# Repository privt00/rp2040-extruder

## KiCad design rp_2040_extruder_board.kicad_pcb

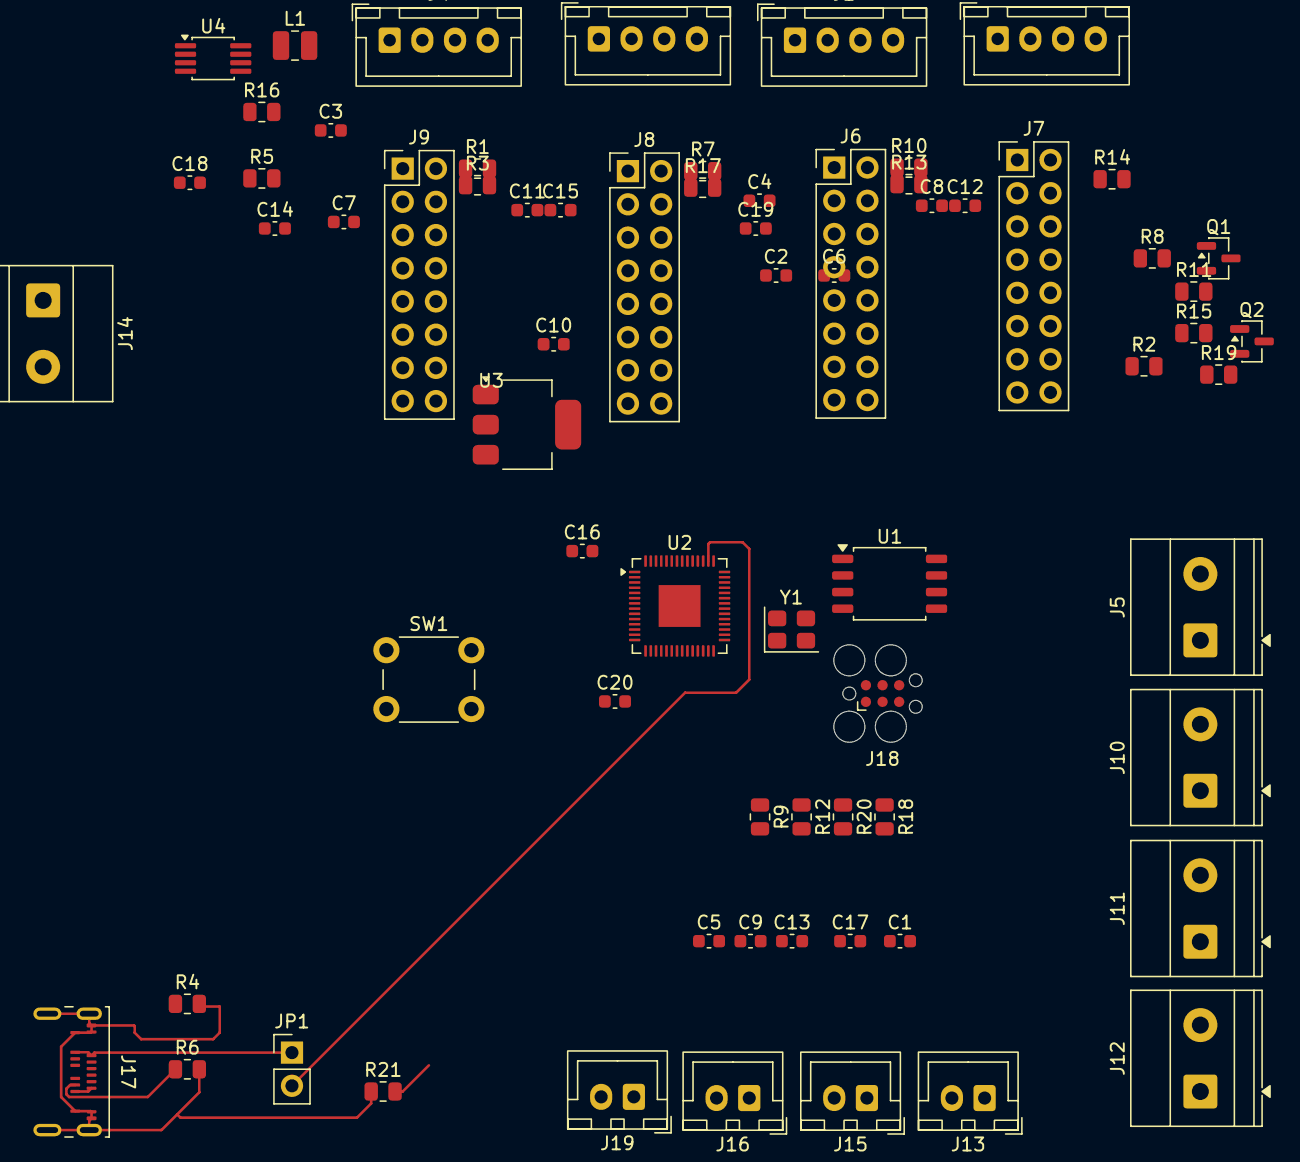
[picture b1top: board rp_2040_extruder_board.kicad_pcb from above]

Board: 2 copper layers, 70 parts (0 on the bottom side), 69 nets.

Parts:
C1, C2, C3, C5, C8, C9, C10, C11, C13, C17, C18, C19: 100nF; C_0603_1608Metric
C4, C7, C12, C15: 47µF; C_0603_1608Metric
C6: 1µF; C_0603_1608Metric
C14: 30µF; C_0603_1608Metric
C16, C20: 22 pF; C_0603_1608Metric
J1, J2, J3, J4: Conn_01x04; JST_XH_B4B-XH-A_1x04_P2.50mm_Vertical
J5, J10, J11, J12, J14: Screw_Terminal_01x02; TerminalBlock_Phoenix_MKDS-1,5-2-5.08_1x02_P5.08mm_Horizont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
J6, J7, J8, J9: Conn_02x08_Odd_Even; PinHeader_2x08_P2.54mm_Vertical
J13, J15, J16, J19: Conn_01x02; JST_XH_B2B-XH-A_1x02_P2.50mm_Vertical
J17: USB_C_Receptacle; USB_C_Receptacle_Amphenol_124019772112A
J18: Conn_ARM_SWD_TagConnect_TC2030; Tag-Connect_TC2030-IDC-FP_2x03_P1.27mm_Vertical
JP1: Jumper_2_Open; PinHeader_1x02_P2.54mm_Vertical
L1: L; L_1008_2520Metric
Q1, Q2: AO3400A; SOT-23
R1, R7, R10, R14: 10kΩ; R_0805_2012Metric
R2, R3, R13, R17: 4.7kΩ; R_0805_2012Metric
R4, R6: 5.1kΩ; R_0805_2012Metric
R5: 10 kΩ; R_0805_2012Metric
R8, R15: 100Ω; R_0805_2012Metric
R9, R12, R18, R20: 4.7k; R_0805_2012Metric
R11, R19: 100kΩ; R_0805_2012Metric
R16: 52.5 kΩ; R_0805_2012Metric
R21: R; R_0805_2012Metric
SW1: SW_Push; SW_PUSH_6mm
U1: W25Q16JVSS; SOIC-8_5.3x5.3mm_P1.27mm
U2: RP2040; QFN-56-1EP_7x7mm_P0.4mm_EP3.2x3.2mm
U3: AMS1117-3.3; SOT-223-3_TabPin2
U4: TPS62160DGK; MSOP-8_3x3mm_P0.65mm
Y1: Crystal; Crystal_SMD_3225-4Pin_3.2x2.5mm

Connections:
+3.3V: C1.2, C2.2, C5.2, C6.2, C9.2, C10.1, C13.2, C17.2, J6.3, J7.3, J8.3, J9.3, J18.1 (VCC), R1.2, R7.2, R10.2, R14.2, U1.8 (VCC), U2.1 (IOVDD), U2.10 (IOVDD), U2.22 (IOVDD), U2.23 (DVDD), U2.33 (IOVDD), U2.42 (IOVDD), U2.43 (ADC_AVDD), U2.48 (USB_VDD), U2.49 (IOVDD), U2.50 (DVDD), U3.2 (VO)
+5V: L1.2, R16.1, U3.3 (VI), U4.6 (VOS)
+12V: C3.2, C4.2, C7.2, C8.2, C11.2, C12.2, C14.1, C15.2, C18.1, C19.2, J5.1, J6.15, J7.15, J8.15, J9.15, J10.1, J11.1, J12.1, J14.1, U4.2 (VIN), U4.3 (EN)
/5V_MAIN: JP1.2 (B), U2.44 (VREG_VIN)
/RX PIN: R2.2, R3.2, R13.2, R17.2, U2.17 (GPIO14)
/VBUS_USB: J17.A4 (VBUS), J17.A9 (VBUS), J17.B4 (VBUS), J17.B9 (VBUS), JP1.1 (A)
GND: C1.1, C2.1, C3.1, C4.1, C5.1, C6.1, C7.1, C8.1, C9.1, C10.2, C11.1, C12.1, C13.1, C14.2, C15.1, C16.2, C17.1, C18.2, C19.1, C20.2, J5.2, J6.1, J6.12, J6.13, J6.14, J7.1, J7.12, J7.13, J7.14, J8.1, J8.12, J8.13, J8.14, J9.1, J9.12, J9.13, J9.14, J10.2, J11.2, J12.2, J13.1, J14.2, J15.1, J16.1, J17.A1 (GND), J17.A12 (GND), J17.B1 (GND), J17.B12 (GND), J17.SH (SHIELD), J18.5 (GND), J19.1, Q1.2 (S), Q1.3 (D), Q2.2 (S), Q2.3 (D), R4.2, R5.2, R6.2, R11.2, R19.2, R21.1, SW1.2, U1.4 (GND), U2.19 (TESTEN), U2.57 (GND), U3.1 (GND), U4.1 (PGND), U4.4 (AGND)
unnamed: J9.2, U2.3 (GPIO1)
unnamed: J9.4, U2.2 (GPIO0)
unnamed: J4.1, J9.5
unnamed: J4.4, J9.7
unnamed: J9.8, R1.1
unnamed: J4.3, J9.9
unnamed: J9.10, R3.1
unnamed: J4.2, J9.11
unnamed: J6.16, J7.16, J8.16, J9.16, U2.11 (GPIO8)
unnamed: J8.2, U2.5 (GPIO3)
unnamed: J8.4, U2.4 (GPIO2)
unnamed: J3.1, J8.5
unnamed: J3.4, J8.7
unnamed: J8.8, R7.1
unnamed: J3.3, J8.9
unnamed: J8.10, R17.1
unnamed: J3.2, J8.11
unnamed: J6.2, U2.7 (GPIO5)
unnamed: J6.4, U2.6 (GPIO4)
unnamed: J1.1, J6.5
unnamed: J1.4, J6.7
unnamed: J6.8, R10.1
unnamed: J1.3, J6.9
unnamed: J6.10, R13.1
unnamed: J1.2, J6.11
unnamed: J7.2, U2.9 (GPIO7)
unnamed: J7.4, R8.2, U2.8 (GPIO6), U2.12 (GPIO9)
unnamed: J7.8, R14.1
unnamed: J7.10, R2.1
unnamed: J17.A5 (CC1), R4.1
unnamed: J17.B5 (CC2), R6.1
unnamed: J17.A8 (SBU1), J17.B8 (SBU2)
unnamed: J2.1, J7.5
unnamed: J2.2, J7.11
unnamed: J2.3, J7.9
unnamed: J2.4, J7.7
unnamed: J18.4 (SWCLK), U2.24 (SWCLK)
unnamed: J18.2 (SWDIO), U2.25 (SWDIO)
unnamed: J18.3 (~RESET), R21.2, SW1.1, U2.26 (RUN)
unnamed: J13.2, R18.2
unnamed: J15.2, R20.2
unnamed: J16.2, R12.2
unnamed: J19.2, R9.2
unnamed: Q1.1 (G), R8.1, R11.1
unnamed: Q2.1 (G), R15.1, R19.1
unnamed: R15.2, U2.13 (GPIO10)
unnamed: R18.1, U2.38 (GPIO26/ADC0)
unnamed: R20.1, U2.39 (GPIO27/ADC1)
unnamed: R12.1, U2.40 (GPIO28/ADC2)
unnamed: R9.1, U2.41 (GPIO29/ADC3)
unnamed: U1.6 (CLK), U2.52 (QSPI_SCLK)
unnamed: U1.5 (DI/IO_{0}), U2.53 (QSPI_SD0)
unnamed: U1.2 (DO/IO_{1}), U2.55 (QSPI_SD1)
unnamed: U1.3 (~WP/IO_{2}), U2.54 (QSPI_SD2)
unnamed: U1.7 (~HOLD/~RESET/IO_{3}), U2.51 (QSPI_SD3)
unnamed: J17.A7 (D-), J17.B7 (D-), U2.46 (USB_DM)
unnamed: J17.A6 (D+), J17.B6 (D+), U2.47 (USB_DP)
unnamed: C16.1, U2.20 (XIN), Y1.2
unnamed: C20.1, U2.21 (XOUT), Y1.1
unnamed: U1.1 (~CS), U2.56 (~QSPI_SS)
unnamed: R5.1, R16.2, U4.5 (FB)
unnamed: L1.1, U4.7 (SW)

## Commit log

2026-04-08 Initial commit: KiCad extruder board
2026-04-08 progress
2026-04-08 more compact
2026-04-08 even more compact
2026-04-08 Added some tracks
